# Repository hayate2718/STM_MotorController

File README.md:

# STM_MotorController
STM_MotorSystem用のstm32f303k8nucleoを用いたコントローラ<br>
クロック周波数は64MHz

|peripheral|pin|
|---|---|
|canrx|PA11(D10)|
|cantx|PA12(D2)|

## MX設定
|config|parameter|
|---|---|
|prescaler|4|
|TQB1|5|
|TQB2|2|
|RSJ|1|
|BaudRate|1Mbps|
|TTC|0|
|ABusOffM|1|
|AWakeUpM|1|
|ARetransission|1|
|RFL|0|
|TFP|0|
|OperatingM||

## 追記
割り込みの有効化忘れないでにゃん（RX0を有効化すればいいんだにゃん）

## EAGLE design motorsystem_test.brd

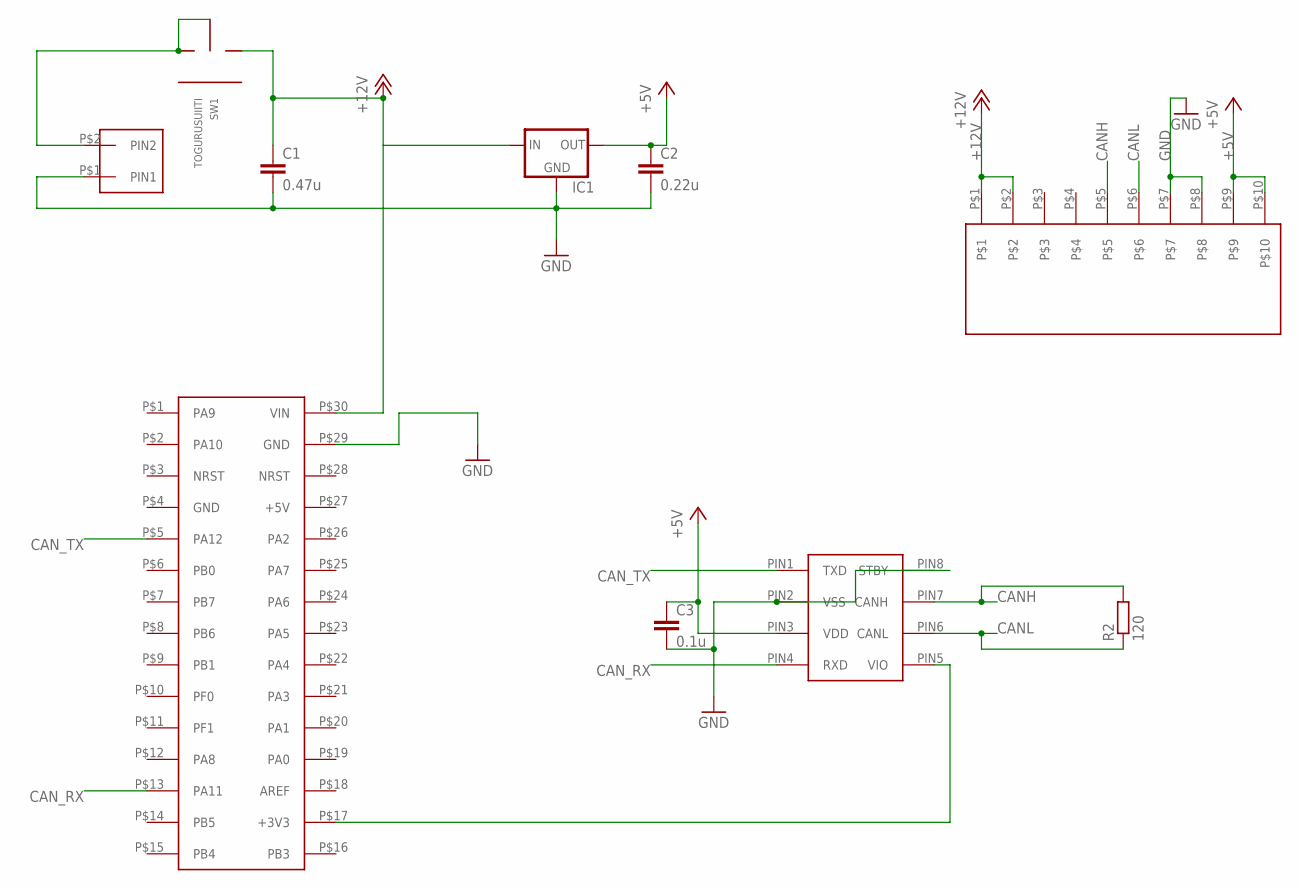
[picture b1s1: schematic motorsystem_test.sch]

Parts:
C1: 0.47u; C025-030X050
C2: 0.22u; C025-030X050
C3: 0.1u; C025-030X050
IC1: 78XXS
IC2: MCP2562; DIL8
R2: 120; 0207/2V
SW1: TOGURUSUIITI
U$1: XH_2P
U$2: BOX10PBOX10P-L; BOX10P-L
U$3: NUCLEO-F303K8; NUCLEO-NANO

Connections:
+5V: C2.1, C3.1, IC1.OUT, IC2.PIN3 (VDD), U$2.P$9, U$2.P$10
+12V: C1.1, IC1.IN, SW1.1, U$2.P$1, U$2.P$2, U$3.P$30 (VIN)
CANH: IC2.PIN7 (CANH), R2.2, U$2.P$5
CANL: IC2.PIN6 (CANL), R2.1, U$2.P$6
CAN_RX: IC2.PIN4 (RXD), U$3.P$13 (PA11)
CAN_TX: IC2.PIN1 (TXD), U$3.P$5 (PA12)
GND: C1.2, C2.2, C3.2, IC1.GND, IC2.PIN2 (VSS), IC2.PIN8 (STBY), U$1.P$1 (PIN1), U$2.P$7, U$2.P$8, U$3.P$29 (GND)
unnamed: SW1.2, SW1.C, U$1.P$2 (PIN2)
unnamed: IC2.PIN5 (VIO), U$3.P$17 (+3V3)

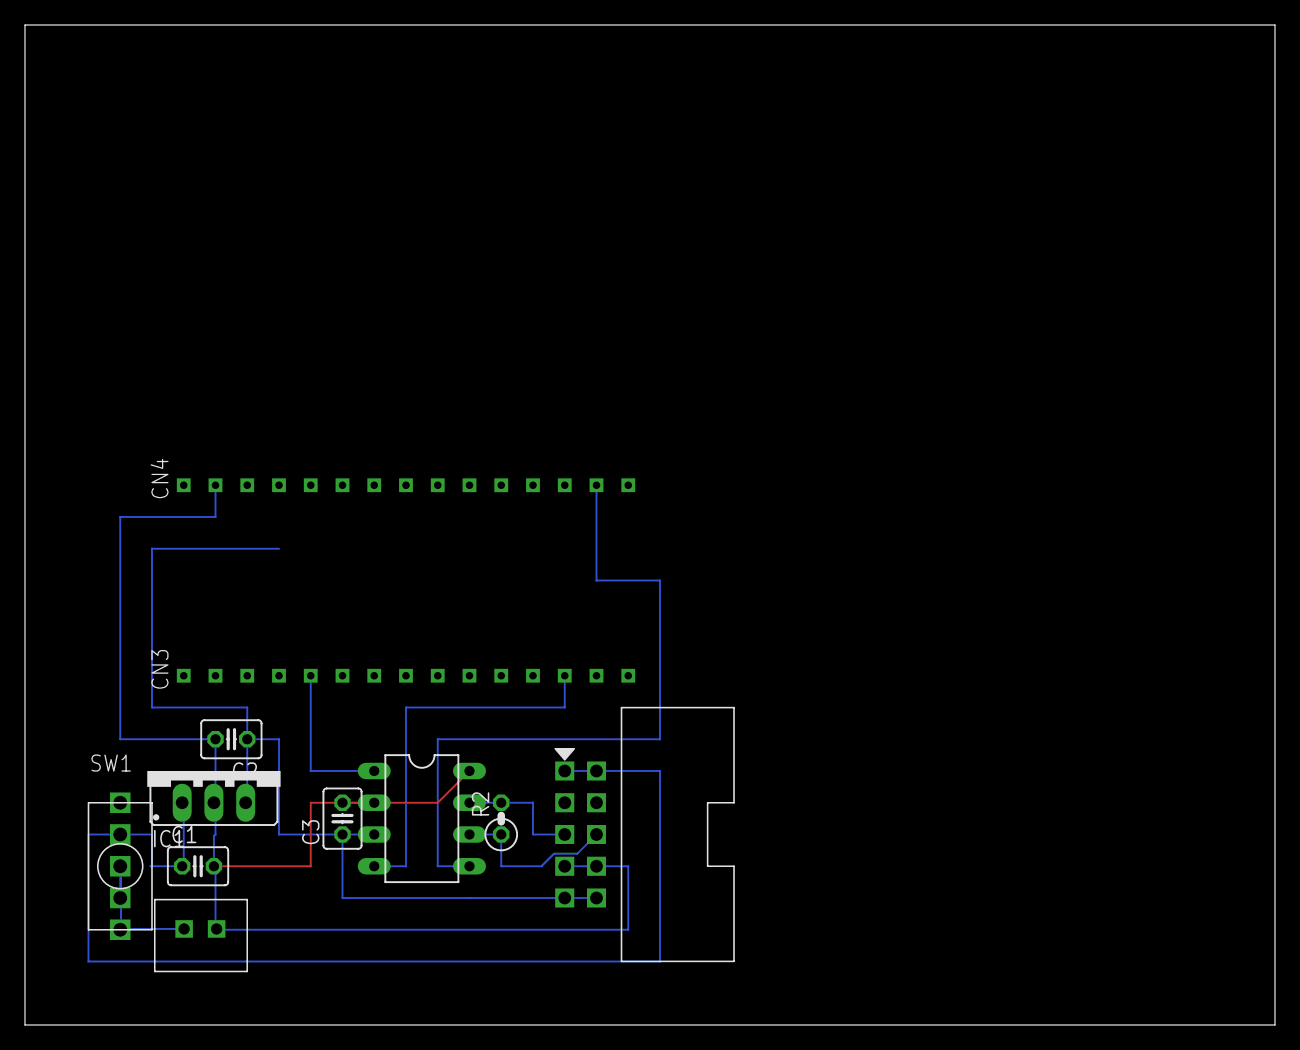
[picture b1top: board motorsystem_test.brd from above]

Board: 2 copper layers, 100.0 x 80.0 mm, 10 parts (0 on the bottom side), 9 nets.

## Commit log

2021-10-23 リポジトリ作成
2021-10-23 図面作成
